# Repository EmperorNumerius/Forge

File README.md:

Please see [hackclub/forge](https://github.com/hackclub/forge)

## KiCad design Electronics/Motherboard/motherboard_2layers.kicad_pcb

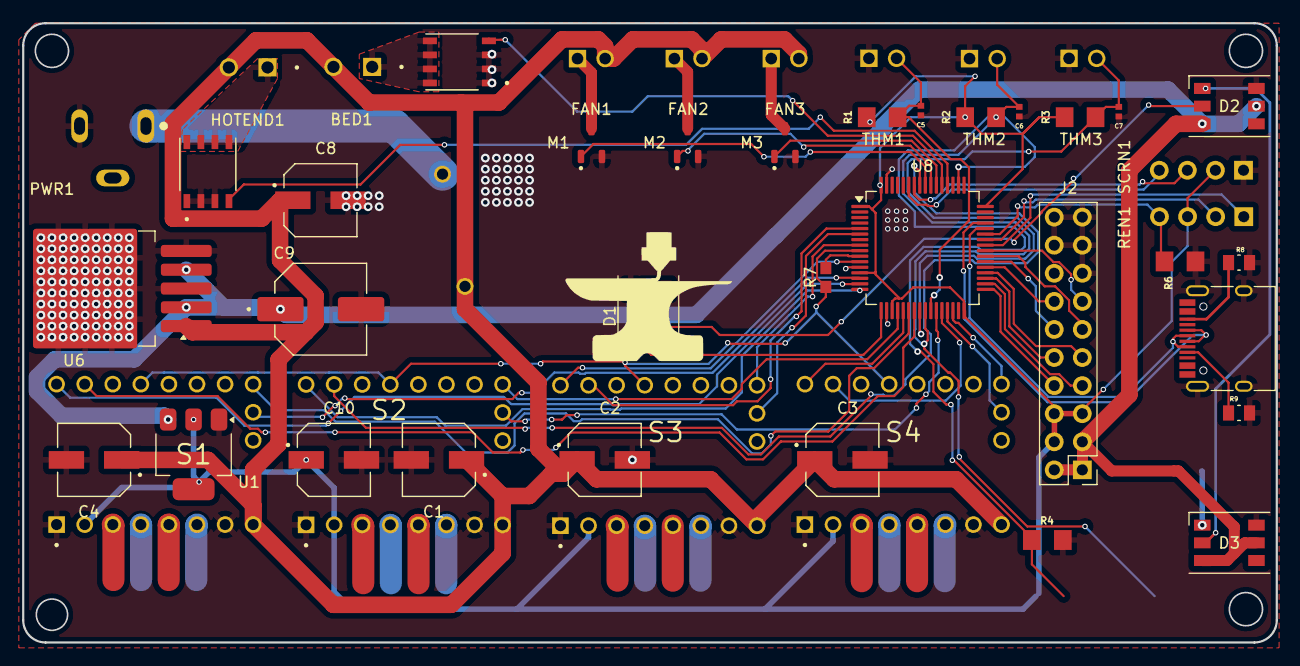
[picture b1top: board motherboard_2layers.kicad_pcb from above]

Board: 2 copper layers, 113.4 x 56.0 mm, 47 parts (1 on the bottom side), 57 nets.

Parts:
BED1: 1751248; PHOENIX_1751248
C1, C2, C3, C4, C8: 100uf 35v; CAP_EEEFT1V101AP
C5, C6, C7: GCM155R71H104KE02J; CAPC1005X55N
C9: 330uf 35v; CAPAE830X1000N
C10: 220uf 16v; CAP_EEEFN1C221XP
D1, D2, D3: WS2812; LED_WS2812_PLCC6_5.0x5.0mm_P1.6mm
F1: RUEF900; FUSRR1015W81L2410T300H2900
FAN1: JST_B2B-XH-A
FAN2, FAN3: B2B-XH-A; JST_B2B-XH-A
HOTEND1: 1751248; PHOENIX_1751248
J2: Conn_02x10_Odd_Even; PinHeader_2x10_P2.54mm_Vertical
M1, M2, M3: AO3400A; SOT95P280X125-3N
PWR1: PJ-102B; CUI_PJ-102B
Q1, Q2: TRANS_FDMS86202
R1, R2, R3: RC1206JR-134K7L; RESC3216X65
R4, R6: 4.7k; RESC3216X65
R7: 1k; 0603
R8, R9: 5.1k; RESC2012X65N
REN1: PEC11H-4015F-S0016; PinHeader_1x04_P2.54mm_Vertical
S1, S2, S3, S4: TMC2209_SILENTSTEPSTICK; MODULE_TMC2209_SILENTSTEPSTICK
SCRN1: SSD1306; PinHeader_1x04_P2.54mm_Vertical
THM1, THM2, THM3: B2B-XH-A; JST_B2B-XH-A
U1: AMS1117-3.3; SOT-223-3_TabPin2
U6: LM2576HVS-5; TO-263-5_TabPin3
U8: STM32F405RGTx; LQFP-64_10x10mm_P0.5mm
USB_C1: TYPE-C-31-M-12; USB_C_Receptacle_HRO_TYPE-C-31-M-12

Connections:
+3V3: C10.1, J2.4, J2.5, J2.6, R1.1, R2.1, R3.1, REN1.3 (S), S1.2 (VIO), S2.2 (VIO), S3.2 (VIO), S4.2 (VIO), SCRN1.2 (VCC), U1.2 (VO), U8.1 (VBAT), U8.13 (VDDA), U8.19 (VDD), U8.32 (VDD), U8.48 (VDD), U8.64 (VDD)
+5V: C9.1, D1.3 (VCC), D1.5 (VDD), D2.3 (VCC), D2.5 (VDD), D3.3 (VCC), D3.5 (VDD), J2.1, J2.2, J2.3, U1.3 (VI), U6.2 (OUT), U6.4 (FB)
BED: Q2.4 (G), U8.53 (PC12)
DIAG_M1: S1.18 (DIAG), U8.14 (PA0)
DIAG_M2: S3.18 (DIAG), U8.6 (PH1)
DIAG_M3: S2.18 (DIAG), U8.27 (PB1)
DIAG_M4: S4.18 (DIAG), U8.29 (PB10)
DIR_M1: S1.9 (DIR), U8.15 (PA1)
DIR_M2: S3.9 (DIR), U8.11 (PC3)
DIR_M3: S2.9 (DIR), U8.16 (PA2)
DIR_M4: S4.9 (DIR), U8.21 (PA5)
EN_BTN: R6.1, REN1.4 (W), U8.43 (PA10)
EN_FOR: REN1.1 (A), U8.41 (PA8)
EN_M1: S1.16 (~EN), U8.22 (PA6)
EN_M2: S3.16 (~EN), U8.8 (PC0)
EN_M3: S2.16 (~EN), U8.20 (PA4)
EN_M4: S4.16 (~EN), U8.30 (PB11)
EN_REV: REN1.2 (B), U8.42 (PA9)
FAN1: M1.1, U8.56 (PB4)
FAN2: M2.1, U8.55 (PB3)
FAN3: M3.1, U8.54 (PD2)
GNDREF: C1.2, C2.2, C3.2, C4.2, C5.2, C6.2, C7.2, C8.2, C9.2, C10.2, D1.6 (VSS), D2.6 (VSS), D3.6 (VSS), J2.15, J2.16, J2.17, J2.18, J2.19, J2.20, M1.2, M2.2, M3.2, PWR1.2, Q1.1 (S), Q1.2 (S), Q1.3 (S), Q2.1 (S), Q2.2 (S), Q2.3 (S), R4.2, R6.2, R8.2, R9.2, S1.1 (GND), S1.7 (GND), S2.1 (GND), S2.7 (GND), S3.1 (GND), S3.7 (GND), S4.1 (GND), S4.7 (GND), SCRN1.1 (GND), THM1.1, THM2.1, THM3.1, U1.1 (GND), U6.3 (GND), U6.5 (~ON/OFF), U8.12 (VSSA), U8.18 (VSS), U8.63 (VSS), USB_C1.S1 (SHIELD)
HOTEND: Q1.4 (G), U8.52 (PC11)
NEOPIXEL_DIN: D1.2 (DIN), U8.17 (PA3)
unnamed: BED1.01, Q2.5 (D), Q2.6 (D), Q2.7 (D), Q2.8 (D)
unnamed: D1.1 (DOUT), D2.2 (DIN)
unnamed: D2.1 (DOUT), D3.2 (DIN)
unnamed: F1.1, PWR1.1
unnamed: FAN1.1, M1.3
unnamed: FAN2.1, M2.3
unnamed: FAN3.1, M3.3
unnamed: HOTEND1.01, Q1.5 (D), Q1.6 (D), Q1.7 (D), Q1.8 (D)
unnamed: R9.1, USB_C1.A5 (CC1)
unnamed: R8.1, USB_C1.B5 (CC2)
PB12: J2.8, U8.33 (PB12)
PB13: J2.7, U8.34 (PB13)
PB14: J2.10, U8.35 (PB14)
PB15: J2.9, U8.36 (PB15)
PC6: J2.14, U8.37 (PC6)
PC7: J2.12, U8.38 (PC7)
PC8: J2.11, U8.39 (PC8)
PC9: J2.13, U8.40 (PC9)
SCRN_SCL: SCRN1.3 (SCL), U8.58 (PB6)
SCRN_SDA: SCRN1.4 (SDA), U8.59 (PB7)
STEP_M1: S1.10 (STEP), U8.23 (PA7)
STEP_M2: S3.10 (STEP), U8.5 (PH0)
STEP_M3: S2.10 (STEP), U8.57 (PB5)
STEP_M4: S4.10 (STEP), U8.28 (PB2)
T0: C7.1, R3.2, THM3.2, U8.24 (PC4)
T1: C6.1, R2.2, THM2.2, U8.25 (PC5)
T2: C5.1, R1.2, THM1.2, U8.26 (PB0)
UART_RX: R7.2, S1.12 (UART), S2.12 (UART), S3.12 (UART), S4.12 (UART), U8.9 (PC1)
UART_TX: R7.1, U8.10 (PC2)
USB_DM: U8.44 (PA11), USB_C1.A7 (DN1), USB_C1.B7 (DN2)
USB_DP: U8.45 (PA12), USB_C1.A6 (DP1), USB_C1.B6 (DP2)
VCC: BED1.02, C1.1, C2.1, C3.1, C4.1, C8.1, F1.2, FAN1.2, FAN2.2, FAN3.2, HOTEND1.02, S1.8 (VM), S2.8 (VM), S3.8 (VM), S4.8 (VM), U6.1 (VIN)
Z_END: R4.1, U8.50 (PA15)

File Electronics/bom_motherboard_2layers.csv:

"Reference","Value","Datasheet","Footprint","Qty","DNP"
"ABL1,FAN2,FAN3,THM1,THM2,THM3,Z_END1","B2B-XH-A","","B2B-XH-A:JST_B2B-XH-A","7",""
"BED1,HOTEND1","1751248","","Phoenix 1751248:PHOENIX_1751248","2",""
"C1,C2,C3,C4,C8","100uf 35v","","CAP_EEEFT1V101AP","5",""
"C5,C6,C7","GCM155R71H104KE02J","","GCM155R71H104KE02J:CAPC1005X55N","3",""
"C9","330uf 35v","","UWT1V101MCL1GS:CAPAE830X1000N","1",""
"C10","220uf 16v","","EEEFN1C221XP:CAP_EEEFN1C221XP","1",""
"D1,D2,D3","WS2812","https://cdn-shop.adafruit.com/datasheets/WS2812.pdf","LED_SMD:LED_WS2812_PLCC6_5.0x5.0mm_P1.6mm","3",""
"FAN1,Q1,Q2","~","","-- mixed values --","3",""
"J2","Conn_02x10_Odd_Even","~","Connector_PinHeader_2.54mm:PinHeader_2x10_P2.54mm_Vertical","1",""
"M1,M2,M3","AO3400A","","AO3400A:SOT95P280X125-3N","3",""
"MOTOR_E1,MOTOR_X1,MOTOR_Y1,MOTOR_Z1","B4B-XH-A","","B4B-XH-A:JST_B4B-XH-A","4",""
"PWR1","PJ-102B","","PJ-102B:CUI_PJ-102B","1",""
"R1,R2,R3","RC1206JR-134K7L","","RC1206JR-134K7L:RESC3216X65","3",""
"R4,R6","4.7k","","RC1206JR-134K7L:RESC3216X65","2",""
"R7","1k","","RC0603FR-131KL:0603","1",""
"R8,R9","5.1k","~","RMCF0805JT5K10:RESC2012X65N","2",""
"REN1","PEC11H-4015F-S0016","PEC11H-4015F-S0016","PinHeader:PinHeader_1x04_P2.54mm_Vertical","1",""
"RGB1","B3B-XH-A","","b3b-xh-a:JST_B3B-XH-A","1",""
"S1,S2,S3,S4","TMC2209_SILENTSTEPSTICK","","TMC2209_SILENTSTEPSTICK:MODULE_TMC2209_SILENTSTEPSTICK","4",""
"SCRN1","SSD1306","","PinHeader:PinHeader_1x04_P2.54mm_Vertical","1",""
"U1","AMS1117-3.3","http://www.advanced-monolithic.com/pdf/ds1117.pdf","Package_TO_SOT_SMD:SOT-223-3_TabPin2","1",""
"U6","LM2576HVS-5","http://www.ti.com/lit/ds/symlink/lm2576.pdf","Package_TO_SOT_SMD:TO-263-5_TabPin3","1",""
"U8","STM32F405RGTx","https://www.st.com/resource/en/datasheet/stm32f405rg.pdf","Package_QFP:LQFP-64_10x10mm_P0.5mm","1",""
"USB_C1","TYPE-C-31-M-12","","Connector_USB:USB_C_Receptacle_HRO_TYPE-C-31-M-12","1",""

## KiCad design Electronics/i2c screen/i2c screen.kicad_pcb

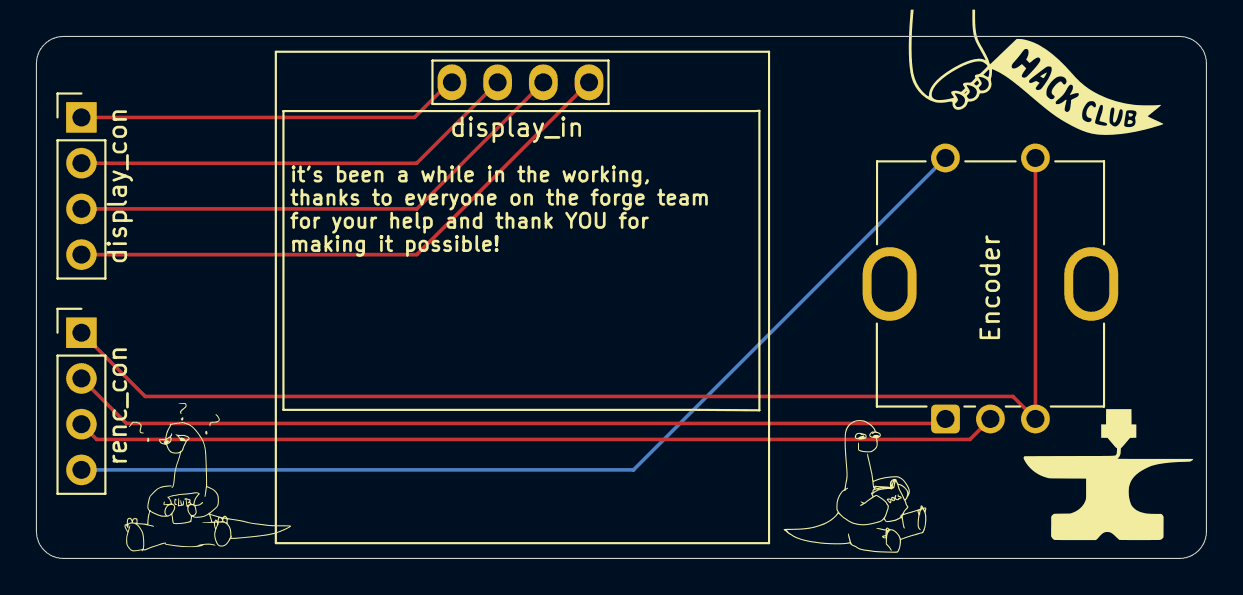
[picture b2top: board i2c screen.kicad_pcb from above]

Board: 2 copper layers, 65.0 x 29.0 mm, 4 parts (0 on the bottom side), 8 nets.

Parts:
J1: renc_con; PinHeader_1x04_P2.54mm_Vertical
J2: display_con; PinHeader_1x04_P2.54mm_Vertical
J3: display_in; 128x64OLED
SW1: Encoder; RotaryEncoder_Bourns_Vertical_PEC12R-3x17F-Sxxxx

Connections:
EN_BTN: J1.4, SW1.S1
EN_FOR: J1.2, SW1.A
EN_REV: J1.3, SW1.C
GNDREF: J1.1, SW1.B, SW1.S2
unnamed: J2.2 (3v3), J3.2
unnamed: J2.1 (gnd), J3.1
unnamed: J2.3 (scl), J3.3
unnamed: J2.4 (sda), J3.4

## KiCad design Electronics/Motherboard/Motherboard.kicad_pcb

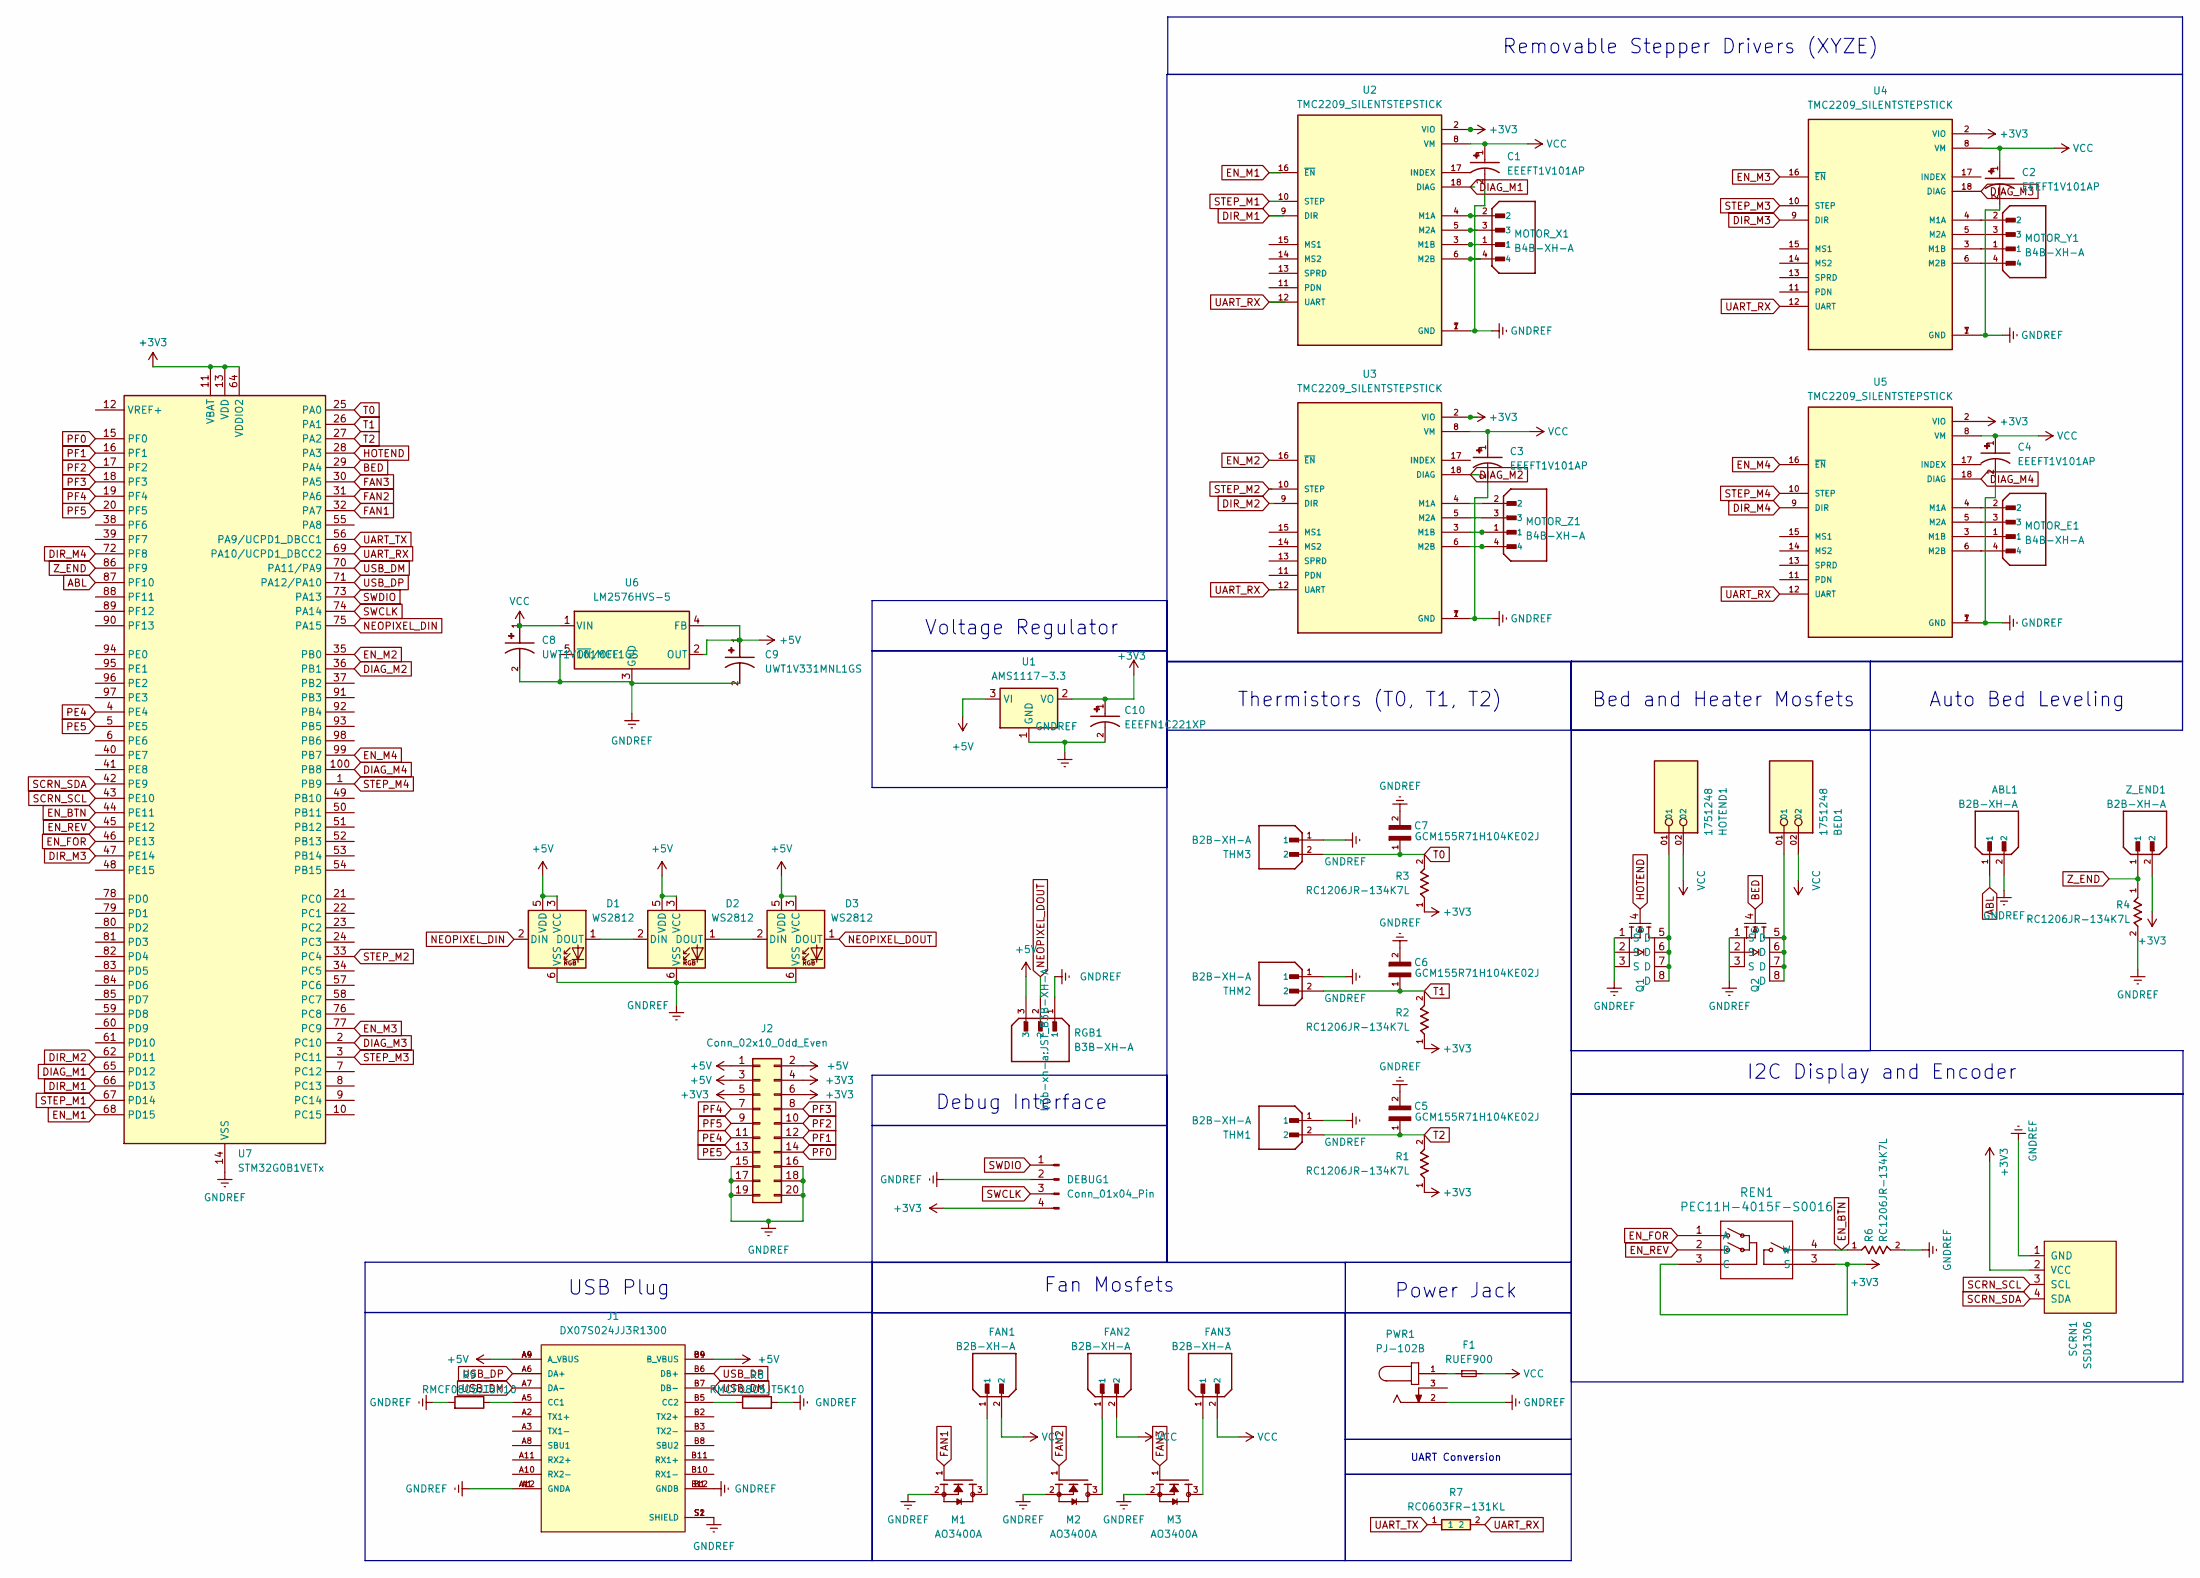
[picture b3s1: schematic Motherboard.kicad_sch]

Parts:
ABL1: B2B-XH-A; JST_B2B-XH-A; PARTREV N/A; DigiKey_Part_Number 455-B2B-XH-A-ND
BED1: 1751248; PHOENIX_1751248; PARTREV 03.03.2021; DigiKey_Part_Number 277-5719-ND
C1, C2, C3, C4: EEEFT1V101AP; CAP_EEEFT1V101AP; PARTREV 10-Oct-19
C5, C6, C7: GCM155R71H104KE02J; CAPC1005X55N; DigiKey_Part_Number 490-14514-2-ND
C8: UWT1V101MCL1GS; CAPAE830X1000N; PARTREV CAT.8100L
C9: UWT1V331MNL1GS; CAPAE830X1000N; PARTREV CAT.8100L
C10: EEEFN1C221XP; CAP_EEEFN1C221XP; PARTREV 10-Oct-19
D1, D2, D3: WS2812; LED_WS2812_PLCC6_5.0x5.0mm_P1.6mm
DEBUG1: Conn_01x04_Pin; PinHeader_1x04_P2.54mm_Vertical
F1: RUEF900; FUSRR1015W81L2410T300H2900
FAN1, FAN2, FAN3: B2B-XH-A; JST_B2B-XH-A; PARTREV N/A; DigiKey_Part_Number 455-B2B-XH-A-ND
HOTEND1: 1751248; PHOENIX_1751248; PARTREV 03.03.2021; DigiKey_Part_Number 277-5719-ND
J1: DX07S024JJ3R1300; JAE_DX07S024JJ3R1300; DigiKey_Part_Number 670-2846-2-ND
J2: Conn_02x10_Odd_Even; PinBox-2.54-02x10-THT
M1, M2, M3: AO3400A; SOT95P280X125-3N; PARTREV L; DigiKey_Part_Number 785-1000-2-ND
MOTOR_E1: B4B-XH-A; JST_B4B-XH-A; PARTREV 7/4/21; DigiKey_Part_Number 455-B4B-XH-A-ND
MOTOR_X1: B4B-XH-A; JST_B4B-XH-A; PARTREV 7/4/21; DigiKey_Part_Number 455-B4B-XH-A-ND
MOTOR_Y1: B4B-XH-A; JST_B4B-XH-A; PARTREV 7/4/21; DigiKey_Part_Number 455-B4B-XH-A-ND
MOTOR_Z1: B4B-XH-A; JST_B4B-XH-A; PARTREV 7/4/21; DigiKey_Part_Number 455-B4B-XH-A-ND
PWR1: PJ-102B; CUI_PJ-102B; PART_REV 1.03; DigiKey_Part_Number CP-102B-ND
Q1, Q2: TRANS_FDMS86202
R1, R2, R3, R4, R6: RC1206JR-134K7L; RESC3216X65; DigiKey_Part_Number 13-RC1206JR-134K7LTR-ND
R7: RC0603FR-131KL; 0603; DigiKey_Part_Number 13-RC0603FR-131KLTR-ND
R8, R9: RMCF0805JT5K10; RESC2012X65N
REN1: PEC11H-4015F-S0016; PinHeader_1x04_P2.54mm_Vertical
RGB1: B3B-XH-A; JST_B3B-XH-A; PARTREV 7/4/21
SCRN1: SSD1306; PinHeader_1x04_P2.54mm_Vertical
THM1, THM2, THM3: B2B-XH-A; JST_B2B-XH-A; PARTREV N/A; DigiKey_Part_Number 455-B2B-XH-A-ND
U1: AMS1117-3.3; SOT-223-3_TabPin2
U2, U3, U4, U5: TMC2209_SILENTSTEPSTICK; MODULE_TMC2209_SILENTSTEPSTICK; PARTREV 1.20
U6: LM2576HVS-5; TO-263-5_TabPin3
U7: STM32G0B1VETx; LQFP-100_14x14mm_P0.5mm
Z_END1: B2B-XH-A; JST_B2B-XH-A; PARTREV N/A; DigiKey_Part_Number 455-B2B-XH-A-ND

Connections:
+3V3: C10.1, DEBUG1.4, J2.4, J2.5, J2.6, R1.1, R2.1, R3.1, REN1.3 (S), SCRN1.2 (VCC), U1.2 (VO), U2.2 (VIO), U3.2 (VIO), U4.2 (VIO), U5.2 (VIO), U7.11 (VBAT), U7.13 (VDD), U7.64 (VDDIO2), Z_END1.2
+5V: C9.1, D1.3 (VCC), D1.5 (VDD), D2.3 (VCC), D2.5 (VDD), D3.3 (VCC), D3.5 (VDD), J1.A4 (A_VBUS), J1.A9 (A_VBUS), J1.B4 (B_VBUS), J1.B9 (B_VBUS), J2.1, J2.2, J2.3, RGB1.3, U1.3 (VI), U6.2 (OUT), U6.4 (FB)
ABL: ABL1.1, U7.87 (PF10)
BED: Q2.4 (G), U7.29 (PA4)
DIAG_M1: U2.18 (DIAG), U7.65 (PD12)
DIAG_M2: U3.18 (DIAG), U7.36 (PB1)
DIAG_M3: U4.18 (DIAG), U7.2 (PC10)
DIAG_M4: U5.18 (DIAG), U7.100 (PB8)
DIR_M1: U2.9 (DIR), U7.66 (PD13)
DIR_M2: U3.9 (DIR), U7.62 (PD11)
DIR_M3: U4.9 (DIR), U7.47 (PE14)
DIR_M4: U5.9 (DIR), U7.72 (PF8)
EN_BTN: R6.1, REN1.4 (W), U7.44 (PE11)
EN_FOR: REN1.1 (A), U7.46 (PE13)
EN_M1: U2.16 (~EN), U7.68 (PD15)
EN_M2: U3.16 (~EN), U7.35 (PB0)
EN_M3: U4.16 (~EN), U7.77 (PC9)
EN_M4: U5.16 (~EN), U7.99 (PB7)
EN_REV: REN1.2 (B), U7.45 (PE12)
FAN1: M1.1, U7.32 (PA7)
FAN2: M2.1, U7.31 (PA6)
FAN3: M3.1, U7.30 (PA5)
GNDREF: ABL1.2, C1.2, C2.2, C3.2, C4.2, C5.2, C6.2, C7.2, C8.2, C9.2, C10.2, D1.6 (VSS), D2.6 (VSS), D3.6 (VSS), DEBUG1.2, J1.A1 (GNDA), J1.A12 (GNDA), J1.B1 (GNDB), J1.B12 (GNDB), J1.S1 (SHIELD), J1.S2 (SHIELD), J2.15, J2.16, J2.17, J2.18, J2.19, J2.20, M1.2, M2.2, M3.2, PWR1.2, R4.2, R6.2, R8.2, R9.2, RGB1.1, SCRN1.1 (GND), THM1.1, THM2.1, THM3.1, U1.1 (GND), U2.1 (GND), U2.7 (GND), U3.1 (GND), U3.7 (GND), U4.1 (GND), U4.7 (GND), U5.1 (GND), U5.7 (GND), U6.3 (GND), U6.5 (~ON/OFF), U7.14 (VSS), U7.63 (VSS)
HOTEND: Q1.4 (G), U7.28 (PA3)
NEOPIXEL_DIN: D1.2 (DIN), U7.75 (PA15)
NEOPIXEL_DOUT: D3.1 (DOUT), RGB1.2
unnamed: BED1.01, Q2.5 (D), Q2.6 (D), Q2.7 (D), Q2.8 (D)
unnamed: D1.1 (DOUT), D2.2 (DIN)
unnamed: D2.1 (DOUT), D3.2 (DIN)
unnamed: F1.1, PWR1.1
unnamed: FAN1.1, M1.3
unnamed: FAN2.1, M2.3
unnamed: FAN3.1, M3.3
unnamed: HOTEND1.01, Q1.5 (D), Q1.6 (D), Q1.7 (D), Q1.8 (D)
unnamed: J1.A5 (CC1), R9.1
unnamed: J1.B5 (CC2), R8.1
unnamed: MOTOR_X1.2, U2.4 (M1A)
unnamed: MOTOR_X1.1, U2.3 (M1B)
unnamed: MOTOR_X1.3, U2.5 (M2A)
unnamed: MOTOR_X1.4, U2.6 (M2B)
unnamed: MOTOR_Z1.2, U3.4 (M1A)
unnamed: MOTOR_Z1.1, U3.3 (M1B)
unnamed: MOTOR_Z1.3, U3.5 (M2A)
unnamed: MOTOR_Z1.4, U3.6 (M2B)
unnamed: MOTOR_Y1.2, U4.4 (M1A)
unnamed: MOTOR_Y1.1, U4.3 (M1B)
unnamed: MOTOR_Y1.3, U4.5 (M2A)
unnamed: MOTOR_Y1.4, U4.6 (M2B)
unnamed: MOTOR_E1.2, U5.4 (M1A)
unnamed: MOTOR_E1.1, U5.3 (M1B)
unnamed: MOTOR_E1.3, U5.5 (M2A)
unnamed: MOTOR_E1.4, U5.6 (M2B)
PE4: J2.11, U7.4 (PE4)
PE5: J2.13, U7.5 (PE5)
PF0: J2.14, U7.15 (PF0)
PF1: J2.12, U7.16 (PF1)
PF2: J2.10, U7.17 (PF2)
PF3: J2.8, U7.18 (PF3)
PF4: J2.7, U7.19 (PF4)
PF5: J2.9, U7.20 (PF5)
SCRN_SCL: SCRN1.3 (SCL), U7.43 (PE10)
SCRN_SDA: SCRN1.4 (SDA), U7.42 (PE9)
STEP_M1: U2.10 (STEP), U7.67 (PD14)
STEP_M2: U3.10 (STEP), U7.33 (PC4)
STEP_M3: U4.10 (STEP), U7.3 (PC11)
STEP_M4: U5.10 (STEP), U7.1 (PB9)
SWCLK: DEBUG1.3, U7.74 (PA14)
SWDIO: DEBUG1.1, U7.73 (PA13)
T0: C7.1, R3.2, THM3.2, U7.25 (PA0)
T1: C6.1, R2.2, THM2.2, U7.26 (PA1)
T2: C5.1, R1.2, THM1.2, U7.27 (PA2)
UART_RX: R7.2, U2.12 (UART), U3.12 (UART), U4.12 (UART), U5.12 (UART), U7.69 (PA10/UCPD1_DBCC2)
UART_TX: R7.1, U7.56 (PA9/UCPD1_DBCC1)
USB_DM: J1.A7 (DA-), J1.B7 (DB-), U7.70 (PA11/PA9)
USB_DP: J1.A6 (DA+), J1.B6 (DB+), U7.71 (PA12/PA10)
VCC: BED1.02, C1.1, C2.1, C3.1, C4.1, C8.1, F1.2, FAN1.2, FAN2.2, FAN3.2, HOTEND1.02, U2.8 (VM), U3.8 (VM), U4.8 (VM), U5.8 (VM), U6.1 (VIN)
Z_END: R4.1, U7.86 (PF9), Z_END1.1

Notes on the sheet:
I2C Display and Encoder
Voltage Regulator
Fan Mosfets
Auto Bed Leveling
Removable Stepper Drivers (XYZE)
Thermistors (T0, T1, T2)
Power Jack
USB Plug
Bed and Heater Mosfets
UART Conversion
Debug Interface

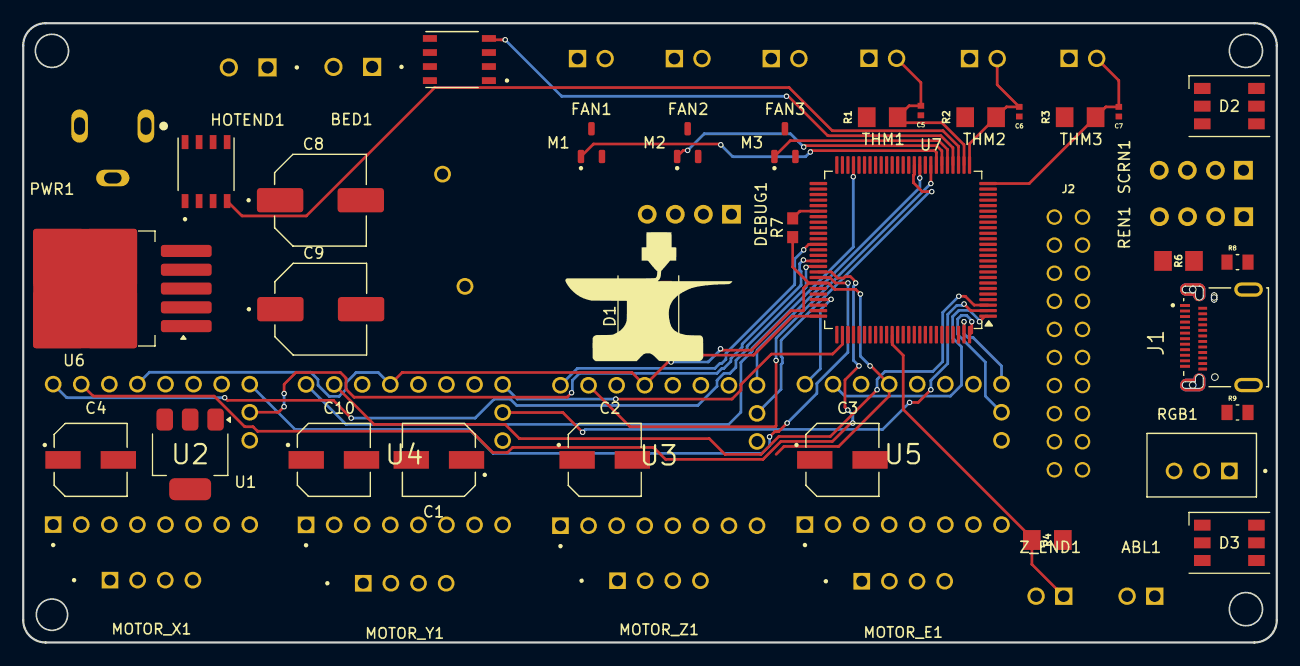
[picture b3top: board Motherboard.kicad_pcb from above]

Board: 2 copper layers, 113.4 x 56.0 mm, 55 parts (1 on the bottom side), 77 nets.

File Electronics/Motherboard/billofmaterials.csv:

"Reference","Value","Datasheet","Footprint","Qty","DNP"
"ABL1,FAN1,FAN2,FAN3,THM1,THM2,THM3,Z_END1","B2B-XH-A",,"B2B-XH-A:JST_B2B-XH-A","8",
"BED1,HOTEND1","1751248",,"Phoenix 1751248:PHOENIX_1751248","2",
"C1,C2,C3,C4","A750MV477M1VAAE018","A750MV477M1VAAE018","footprints:CAP_A750MV477M1VAAE018_KEM","4",
"C5,C6,C7","GCM155R71H104KE02J",,"GCM155R71H104KE02J:CAPC1005X55N","3",
"DEBUG1","Conn_01x04_Pin","~","PinHeader:PinHeader_1x04_P2.54mm_Vertical","1",
"J1","DX07S024JJ3R1300",,"DX07S024JJ3R1300:JAE_DX07S024JJ3R1300","1",
"M1,M2,M3","AO3400A",,"AO3400A:SOT95P280X125-3N","3",
"MCU1","STM32H563VITx","https://www.st.com/resource/en/datasheet/stm32h563vi.pdf","Package_QFP:LQFP-100_14x14mm_P0.5mm","1",
"MOTOR_E1,MOTOR_X1,MOTOR_Y1,MOTOR_Z1","B4B-XH-A",,"B4B-XH-A:JST_B4B-XH-A","4",
"PWR1","PJ-102B",,"PJ-102B:CUI_PJ-102B","1",
"Q1,Q2","IRFH7440TRPBF",,"IRFH7440TRPBF:TRANS_FDMS86202","2",
"R1,R2,R3,R4,R5,R6","RC1206JR-134K7L",,"RC1206JR-134K7L:RESC3216X65","6",
"R7","RC0603FR-131KL",,"RC0603FR-131KL:0603","1",
"R8,R9","RMCF0805JT5K10","~","RMCF0805JT5K10:RESC2012X65N","2",
"REN1","PEC11H-4015F-S0016","PEC11H-4015F-S0016","PinHeader:PinHeader_1x04_P2.54mm_Vertical","1",
"SCRN1","SSD1306",,"PinHeader:PinHeader_1x04_P2.54mm_Vertical","1",
"U1","LM2576S-3.3_NOPB",,"LM2576S-3.3_NOPB:VREG_TPS79625KTTR","1",
"U2,U3,U4,U5","TMC2209_SILENTSTEPSTICK",,"TMC2209_SILENTSTEPSTICK:MODULE_TMC2209_SILENTSTEPSTICK","4",

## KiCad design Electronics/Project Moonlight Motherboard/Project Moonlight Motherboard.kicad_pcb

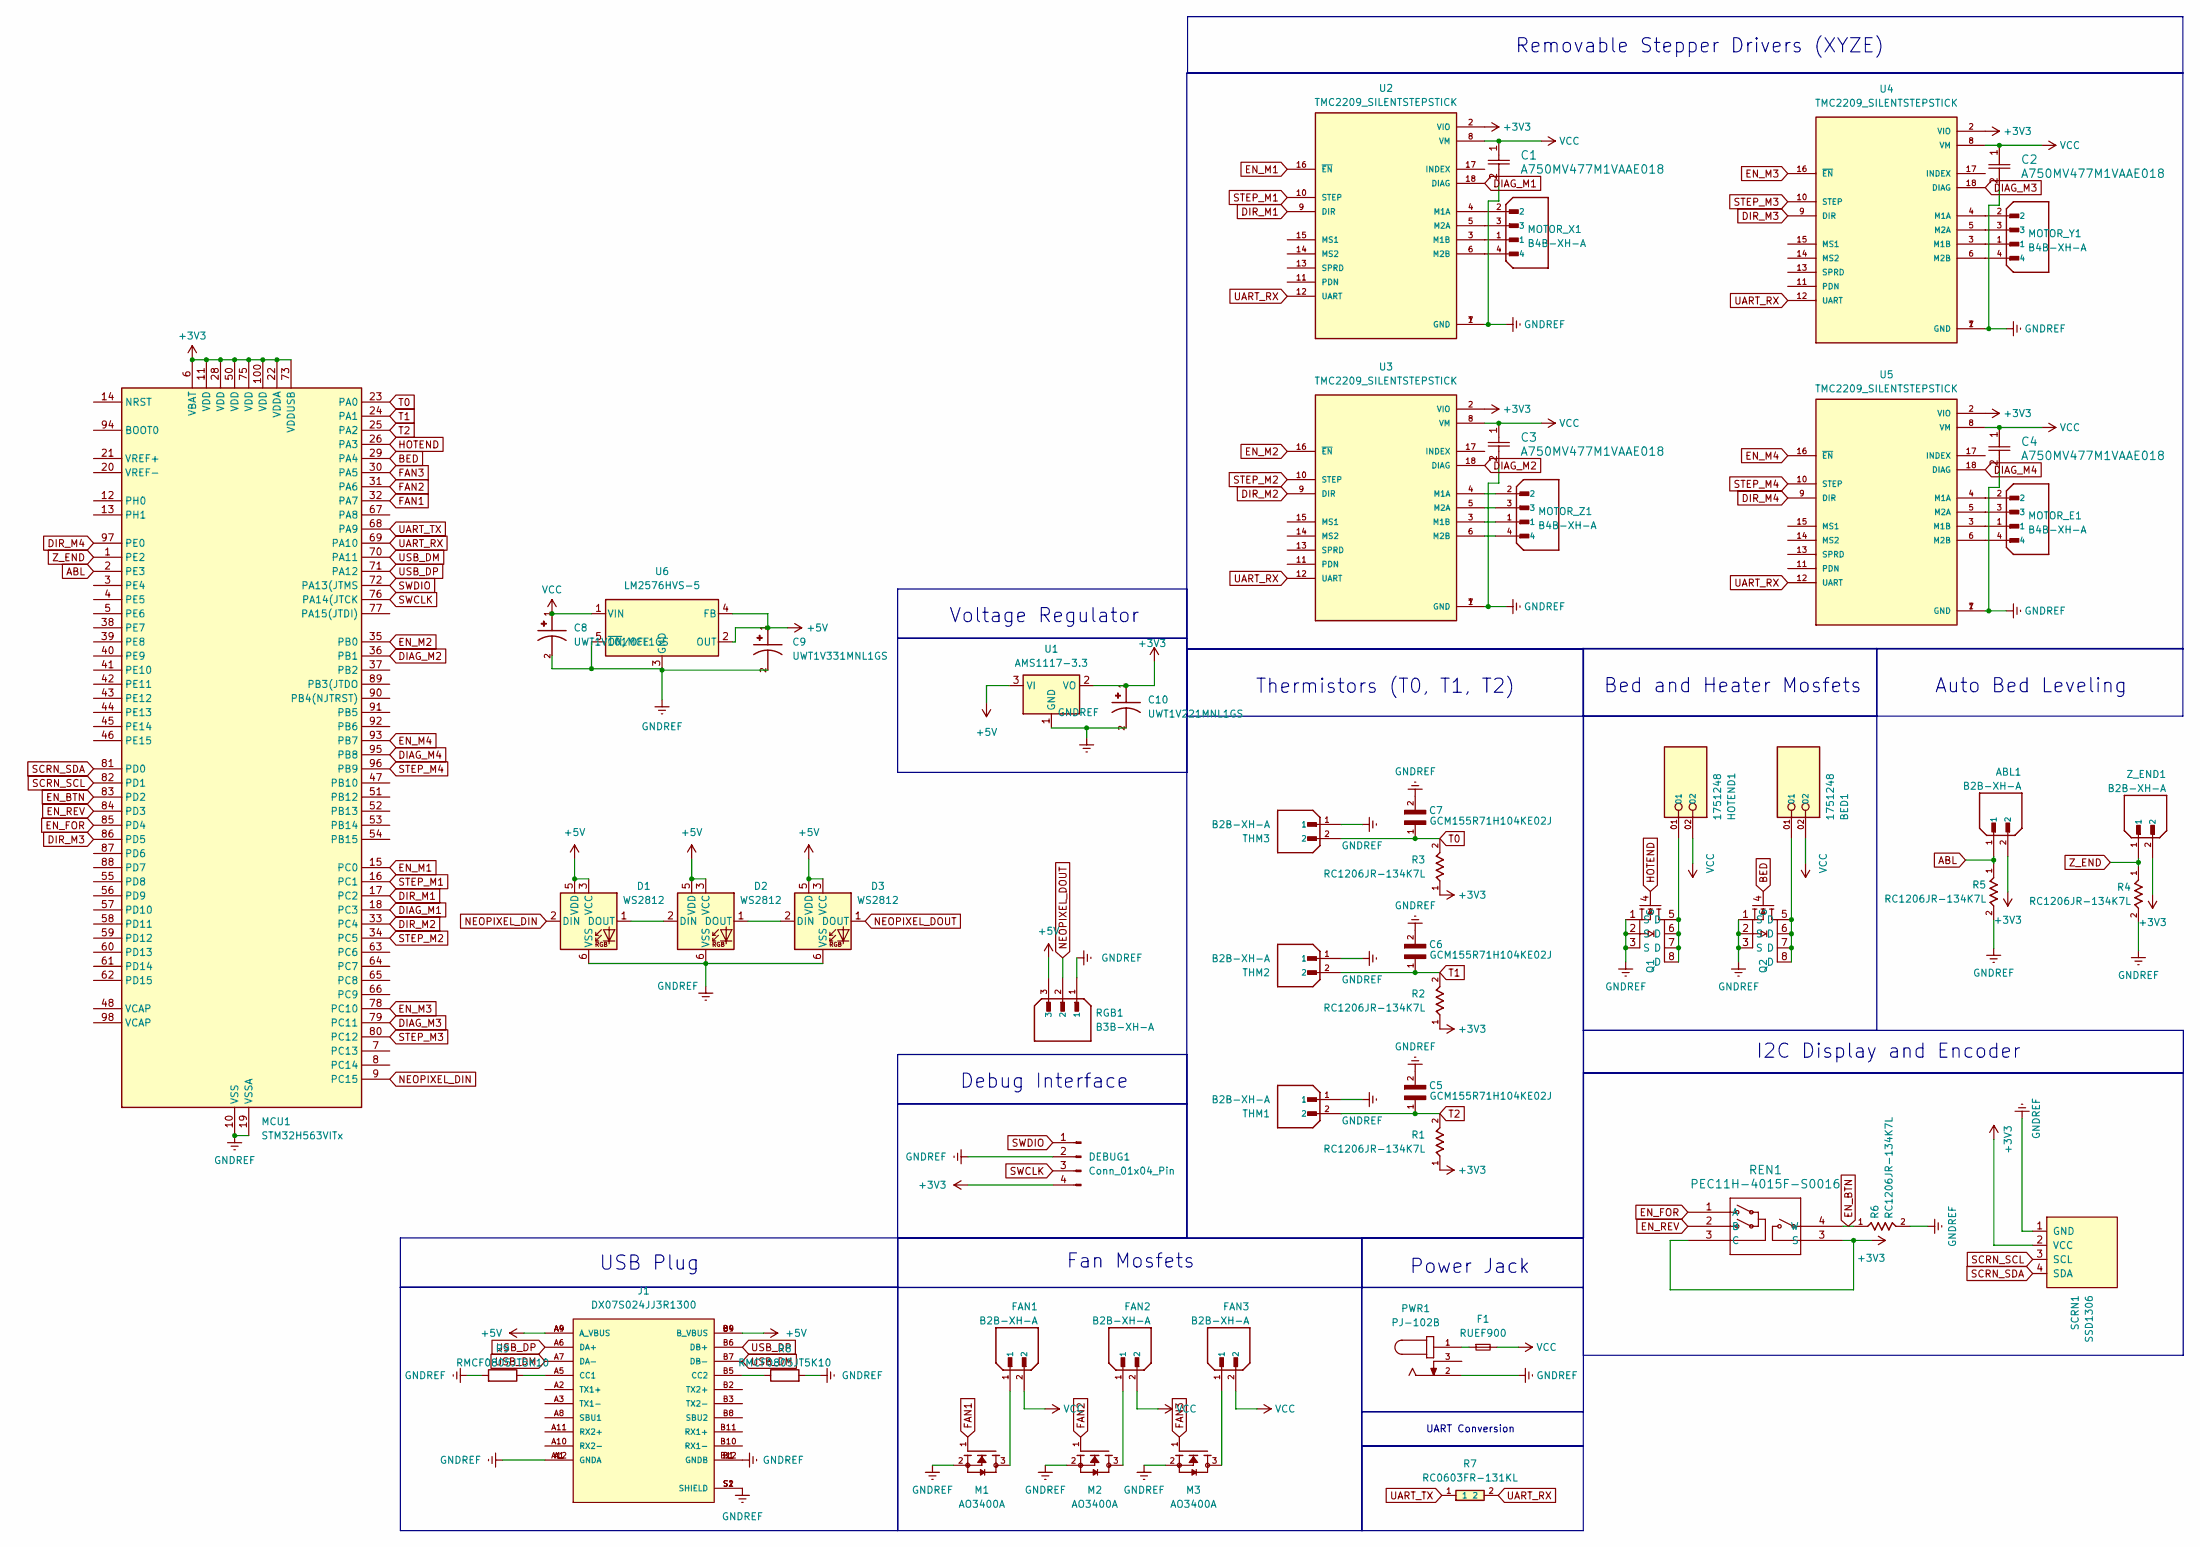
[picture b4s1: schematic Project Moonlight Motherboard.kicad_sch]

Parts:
ABL1: B2B-XH-A; JST_B2B-XH-A; PARTREV N/A; DigiKey_Part_Number 455-B2B-XH-A-ND
BED1: 1751248; PHOENIX_1751248; PARTREV 03.03.2021; DigiKey_Part_Number 277-5719-ND
C1, C2, C3, C4: A750MV477M1VAAE018; CAP_A750MV477M1VAAE018_KEM
C5, C6, C7: GCM155R71H104KE02J; CAPC1005X55N; DigiKey_Part_Number 490-14514-2-ND
C8: UWT1V101MCL1GS; CAPAE830X1000N; PARTREV CAT.8100L
C9: UWT1V331MNL1GS; CAPAE830X1000N; PARTREV CAT.8100L
C10: UWT1V221MNL1GS; PARTREV CAT.8100L
D1, D2, D3: WS2812; LED_WS2812_PLCC6_5.0x5.0mm_P1.6mm
DEBUG1: Conn_01x04_Pin; PinHeader_1x04_P2.54mm_Vertical
F1: RUEF900; FUSRR1015W81L2410T300H2900
FAN1, FAN2, FAN3: B2B-XH-A; JST_B2B-XH-A; PARTREV N/A; DigiKey_Part_Number 455-B2B-XH-A-ND
HOTEND1: 1751248; PHOENIX_1751248; PARTREV 03.03.2021; DigiKey_Part_Number 277-5719-ND
J1: DX07S024JJ3R1300; JAE_DX07S024JJ3R1300; DigiKey_Part_Number 670-2846-2-ND
M1, M2, M3: AO3400A; SOT95P280X125-3N; PARTREV L; DigiKey_Part_Number 785-1000-2-ND
MCU1: STM32H563VITx; LQFP-100_14x14mm_P0.5mm
MOTOR_E1: B4B-XH-A; JST_B4B-XH-A; PARTREV 7/4/21; DigiKey_Part_Number 455-B4B-XH-A-ND
MOTOR_X1: B4B-XH-A; JST_B4B-XH-A; PARTREV 7/4/21; DigiKey_Part_Number 455-B4B-XH-A-ND
MOTOR_Y1: B4B-XH-A; JST_B4B-XH-A; PARTREV 7/4/21; DigiKey_Part_Number 455-B4B-XH-A-ND
MOTOR_Z1: B4B-XH-A; JST_B4B-XH-A; PARTREV 7/4/21; DigiKey_Part_Number 455-B4B-XH-A-ND
PWR1: PJ-102B; CUI_PJ-102B; PART_REV 1.03; DigiKey_Part_Number CP-102B-ND
Q1, Q2: TRANS_FDMS86202
R1, R2, R3, R4, R5, R6: RC1206JR-134K7L; RESC3216X65; DigiKey_Part_Number 13-RC1206JR-134K7LTR-ND
R7: RC0603FR-131KL; 0603; DigiKey_Part_Number 13-RC0603FR-131KLTR-ND
R8, R9: RMCF0805JT5K10; RESC2012X65N
REN1: PEC11H-4015F-S0016; PinHeader_1x04_P2.54mm_Vertical
RGB1: B3B-XH-A; JST_B3B-XH-A; PARTREV 7/4/21
SCRN1: SSD1306; PinHeader_1x04_P2.54mm_Vertical
THM1, THM2, THM3: B2B-XH-A; JST_B2B-XH-A; PARTREV N/A; DigiKey_Part_Number 455-B2B-XH-A-ND
U1: AMS1117-3.3; SOT-223-3_TabPin2
U2, U3, U4, U5: TMC2209_SILENTSTEPSTICK; MODULE_TMC2209_SILENTSTEPSTICK; PARTREV 1.20
U6: LM2576HVS-5; TO-263-5_TabPin3
Z_END1: B2B-XH-A; JST_B2B-XH-A; PARTREV N/A; DigiKey_Part_Number 455-B2B-XH-A-ND

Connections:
+3V3: ABL1.2, C10.1, DEBUG1.4, MCU1.6 (VBAT), MCU1.11 (VDD), MCU1.22 (VDDA), MCU1.28 (VDD), MCU1.50 (VDD), MCU1.73 (VDDUSB), MCU1.75 (VDD), MCU1.100 (VDD), R1.1, R2.1, R3.1, REN1.3 (C), SCRN1.2 (VCC), U1.2 (VO), U2.2 (VIO), U3.2 (VIO), U4.2 (VIO), U5.2 (VIO), Z_END1.2
+5V: C9.1, D1.3 (VCC), D1.5 (VDD), D2.3 (VCC), D2.5 (VDD), D3.3 (VCC), D3.5 (VDD), J1.A4 (A_VBUS), J1.A9 (A_VBUS), J1.B4 (B_VBUS), J1.B9 (B_VBUS), RGB1.3, U1.3 (VI), U6.2 (OUT), U6.4 (FB)
ABL: ABL1.1, MCU1.2 (PE3), R5.1
BED: MCU1.29 (PA4), Q2.4 (G)
DIAG_M1: MCU1.18 (PC3), U2.18 (DIAG)
DIAG_M2: MCU1.36 (PB1), U3.18 (DIAG)
DIAG_M3: MCU1.79 (PC11), U4.18 (DIAG)
DIAG_M4: MCU1.95 (PB8), U5.18 (DIAG)
DIR_M1: MCU1.17 (PC2), U2.9 (DIR)
DIR_M2: MCU1.33 (PC4), U3.9 (DIR)
DIR_M3: MCU1.86 (PD5), U4.9 (DIR)
DIR_M4: MCU1.97 (PE0), U5.9 (DIR)
EN_BTN: MCU1.83 (PD2), R6.1, REN1.4 (W)
EN_FOR: MCU1.85 (PD4), REN1.1 (A)
EN_M1: MCU1.15 (PC0), U2.16 (~EN)
EN_M2: MCU1.35 (PB0), U3.16 (~EN)
EN_M3: MCU1.78 (PC10), U4.16 (~EN)
EN_M4: MCU1.93 (PB7), U5.16 (~EN)
EN_REV: MCU1.84 (PD3), REN1.2 (B)
FAN1: M1.1, MCU1.32 (PA7)
FAN2: M2.1, MCU1.31 (PA6)
FAN3: M3.1, MCU1.30 (PA5)
GNDREF: C1.2, C2.2, C3.2, C4.2, C5.2, C6.2, C7.2, C8.2, C9.2, C10.2, D1.6 (VSS), D2.6 (VSS), D3.6 (VSS), DEBUG1.2, J1.A1 (GNDA), J1.A12 (GNDA), J1.B1 (GNDB), J1.B12 (GNDB), J1.S1 (SHIELD), J1.S2 (SHIELD), M1.2, M2.2, M3.2, MCU1.10 (VSS), MCU1.19 (VSSA), MCU1.27 (VSS), MCU1.49 (VSS), MCU1.74 (VSS), MCU1.99 (VSS), PWR1.2, Q1.1 (S), Q1.2 (S), Q1.3 (S), Q2.1 (S), Q2.2 (S), Q2.3 (S), R4.2, R5.2, R6.2, R8.2, R9.2, RGB1.1, SCRN1.1 (GND), THM1.1, THM2.1, THM3.1, U1.1 (GND), U2.1 (GND), U2.7 (GND), U3.1 (GND), U3.7 (GND), U4.1 (GND), U4.7 (GND), U5.1 (GND), U5.7 (GND), U6.3 (GND), U6.5 (~ON/OFF)
HOTEND: MCU1.26 (PA3), Q1.4 (G)
NEOPIXEL_DIN: D1.2 (DIN), MCU1.9 (PC15)
NEOPIXEL_DOUT: D3.1 (DOUT), RGB1.2
unnamed: BED1.01, Q2.5 (D), Q2.6 (D), Q2.7 (D), Q2.8 (D)
unnamed: D1.1 (DOUT), D2.2 (DIN)
unnamed: D2.1 (DOUT), D3.2 (DIN)
unnamed: F1.1, PWR1.1
unnamed: FAN1.1, M1.3
unnamed: FAN2.1, M2.3
unnamed: FAN3.1, M3.3
unnamed: HOTEND1.01, Q1.5 (D), Q1.6 (D), Q1.7 (D), Q1.8 (D)
unnamed: J1.A5 (CC1), R9.1
unnamed: J1.B5 (CC2), R8.1
unnamed: MOTOR_X1.2, U2.4 (M1A)
unnamed: MOTOR_X1.1, U2.3 (M1B)
unnamed: MOTOR_X1.3, U2.5 (M2A)
unnamed: MOTOR_X1.4, U2.6 (M2B)
unnamed: MOTOR_Z1.2, U3.4 (M1A)
unnamed: MOTOR_Z1.1, U3.3 (M1B)
unnamed: MOTOR_Z1.3, U3.5 (M2A)
unnamed: MOTOR_Z1.4, U3.6 (M2B)
unnamed: MOTOR_Y1.2, U4.4 (M1A)
unnamed: MOTOR_Y1.1, U4.3 (M1B)
unnamed: MOTOR_Y1.3, U4.5 (M2A)
unnamed: MOTOR_Y1.4, U4.6 (M2B)
unnamed: MOTOR_E1.2, U5.4 (M1A)
unnamed: MOTOR_E1.1, U5.3 (M1B)
unnamed: MOTOR_E1.3, U5.5 (M2A)
unnamed: MOTOR_E1.4, U5.6 (M2B)
SCRN_SCL: MCU1.82 (PD1), SCRN1.3 (SCL)
SCRN_SDA: MCU1.81 (PD0), SCRN1.4 (SDA)
STEP_M1: MCU1.16 (PC1), U2.10 (STEP)
STEP_M2: MCU1.34 (PC5), U3.10 (STEP)
STEP_M3: MCU1.80 (PC12), U4.10 (STEP)
STEP_M4: MCU1.96 (PB9), U5.10 (STEP)
SWCLK: DEBUG1.3, MCU1.76 (PA14(JTCK)
SWDIO: DEBUG1.1, MCU1.72 (PA13(JTMS)
T0: C7.1, MCU1.23 (PA0), R3.2, THM3.2
T1: C6.1, MCU1.24 (PA1), R2.2, THM2.2
T2: C5.1, MCU1.25 (PA2), R1.2, THM1.2
UART_RX: MCU1.69 (PA10), R7.2, U2.12 (UART), U3.12 (UART), U4.12 (UART), U5.12 (UART)
UART_TX: MCU1.68 (PA9), R7.1
USB_DM: J1.A7 (DA-), J1.B7 (DB-), MCU1.70 (PA11)
USB_DP: J1.A6 (DA+), J1.B6 (DB+), MCU1.71 (PA12)
VCC: BED1.02, C1.1, C2.1, C3.1, C4.1, C8.1, F1.2, FAN1.2, FAN2.2, FAN3.2, HOTEND1.02, U2.8 (VM), U3.8 (VM), U4.8 (VM), U5.8 (VM), U6.1 (VIN)
Z_END: MCU1.1 (PE2), R4.1, Z_END1.1

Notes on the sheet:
I2C Display and Encoder
Voltage Regulator
Fan Mosfets
Auto Bed Leveling
Removable Stepper Drivers (XYZE)
Thermistors (T0, T1, T2)
Power Jack
USB Plug
Bed and Heater Mosfets
UART Conversion
Debug Interface

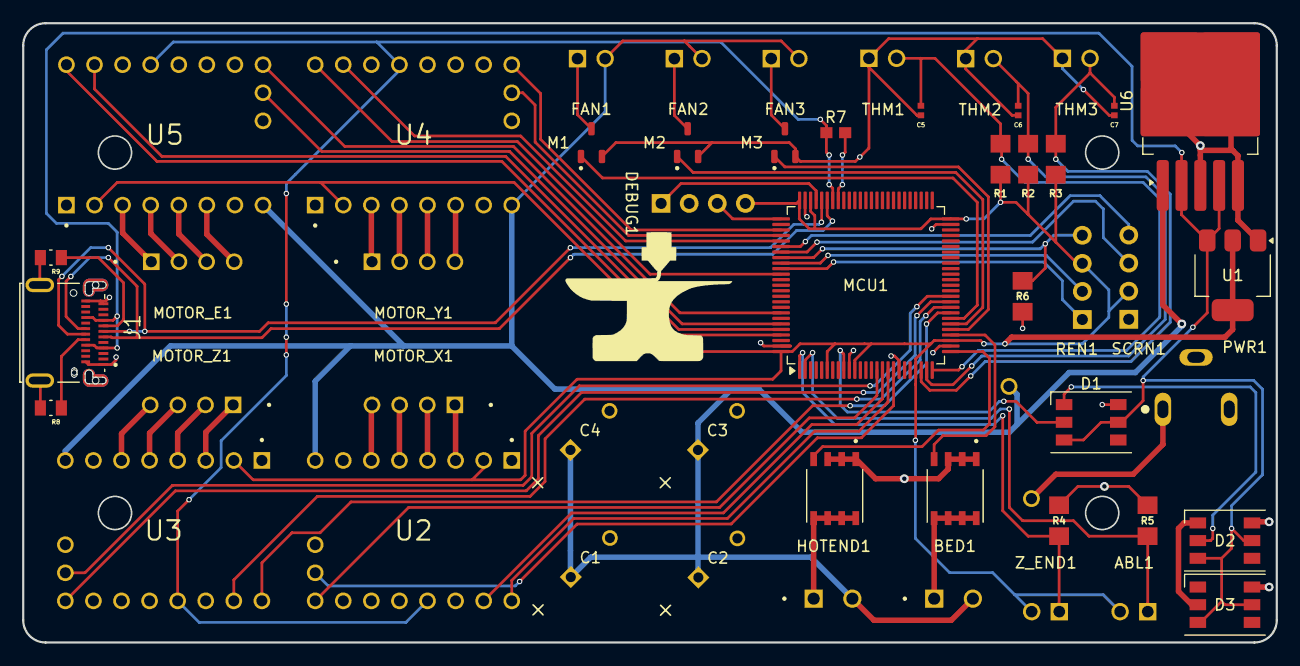
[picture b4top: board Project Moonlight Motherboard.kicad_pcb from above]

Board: 4 copper layers, 113.4 x 56.0 mm, 51 parts (1 on the bottom side), 68 nets.
